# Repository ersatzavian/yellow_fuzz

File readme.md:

# Graduator

## What?

A bass fuzz for my good friend! Don't tell him, it's a surprise. Starting with a Boss MT-2 (I know, ew, don't tell anybody) because that's allegedly how Arion Salazar got most of his fuzz tone's on Third Eye Blind's self-titled (check out 2:20-2:30 in Graduate, of 4:10 in Thanks a Lot if you like yours with phaser). Hell yeah we want that, don't pretend you don't like that record. 

Formerly "yellow fuzz" after BRC's "yellow bikes" that happen to be green. Didn't like the sound of it, now it's the Graduator.

### Rev 01

Rev01 (non form-factor) has been built, brought up, and play tested. 

## Rev01 User Guide

[Electric Druid](https://electricdruid.net/boss-mt-2-metal-zone-pedal-analysis/) has an awesome write-up on the key circuit blocks in the original MT-2 design that's worth a read. If you want a comprehensive survey of the guts of this pedal, read that, then the mods section below, and you're done. 

### Controls

Controls are described by order in the signal chain, rather than physical layout. 

| Control | Original MT-2 Control, or Experiment | Circuit Block | What's it Do? |
| ------- | ------------------------------------ | ------------- | ------------- |
| Gain | Experiment | Distortion Block - First Op-Amp Stage Gain, P1.  | The "pre-distortion" gain block does two things: <ul><li> Applies a band-pass-filtered boost (the center frequency of this boost has a mod described separately). </li><li> Demands enough gain from op amp U1A to cause some distortion when at high gain setttings. </li></ul> In the original MT-2, the gain of this stage is fixed. In the graduator, the feedback resistance here can be reduced, which reduces the gain. If the pre-boost filter is ignored (or the pre-boost filter select switch is used to skip the pre-boost filter), this control doesn't really do much at all; the end result of reducing the gain here is audibly identical to reducing the "Distortion" control. But with a filter selected, this control lets you choose how much that initial band-pass boosts, which can be kind of interesting. Definitely won't be included in the form factor design, but merits playing around with while you're playing the the pre-boost filter select. |
| Pre-Boost Filter Select | Experiment | Distortion Block - First Op-Amp Stage Gyrator Select, SW1.  | As you can read about [here](https://sound-au.com/articles/gyrator-filters.htm), "gyrators" are nifty little active circuit blocks that let you make a thing that acts like an inductor out of a capacitor and a transistor or op-amp. Why not just use an inductor is a good question and is covered in that guide in good detail. For our purposes here, this control lets you pick between two filters, or a third disable setting: <ul><li> A stock filter which is described in the electric druid guide; it's a 36dB boost centered at 1 kHz with a "Q" of 2.8 ("Q", or "Quality Factor" describes how narrow and pointy that bandpass's frequency response is; a filter with high "Q" will be super pointy and really impact just its center frequency, while a filter with lower "Q" will be more gradual and wide and impact frequencies up and down the band around its center.).</li><li> A modified filter: 36 dB boost centered at 224 kHz, with a Q of 3.2. I made this mod to push the boost down into a range I thought might be better for a bass fuzz. </li><li> The disable setting just floats the switch terminal, which is kinda a bug because it takes the feedback (the "gain" control) out of the mix. You'll notice some volume variation going to and from this setting depending on where the "gain" is set. I may fix it. I may not. </li></ul>A bonus feature of this section is that one or both of these filter blocks could be retuned by changing a few parts, letting you do A/B comparison between a setting you like and a new setting you're considering. |
| Distortion | Original | Distortion Block - Second Op-Amp Stage Gain, P2A/B.  | Controls the gain of the second op-amp stage before the diode limiter that really clips the signal. Running this op-amp at high gain will boost the signal to the "rails", and you'll get very hard, square peaks, before you even hit the diode limiter. There are many different sources of distortion in this pedal, it's definitely not all up to just one circuit block to hammer your signal into a mess. |
| Diode Select Switches | Experiment | Distortion Block - Diode Limiting Stage, SW2 / SW3  | The core of this pedal, as with many distortion pedals, is the diode limiter. This stage takes your nice sine-shaped waveform and clips the peaks off of it when they exceed the forward voltage of the diodes. Different diodes have different forward voltages, and different response "shapes" as they effectively turn on and off. The internet is full of forums where people will swear that this diode does this or that and sounds this way or that way, and many of them are subjectively right but nearly all of them are oversimplifying the test case they're talking about. Since there are so many sources of distortion in this (and every) circuit, you're hearing them all. The diode is just part of it. Anyway, this mod lets you pick between three different kinds of diode for your limiter. Even weirder, it lets you choose the diode for the top and bottom half of your waveform separately, so you can produce very "asymmetric" distortion. Right now, you have: <ul><li> A Silicon diode, the generic [1N4148](https://www.diodes.com/assets/Datasheets/ds12019.pdf), with a forward voltage around 1V. </li><li> A Germanium diode, the generic [1N34A](https://www.nteinc.com/specs/original/1N34A.pdf), with a forward voltage around 1V. </li><li> An LED, [Kingbright WP7113QBC/D](https://www.mouser.com/datasheet/2/216/WP7113QBC-D-58299.pdf). This is a blue LED, and has a forward voltage of not less than 2.4V. This is really a bug; I should have used a red or yellow LED with a forward voltage closer to the other two, so that you could compare tone without comparing volume - you'll notice right away that the blue LED is louder than the other diodes. I like how it sounds, though, so I'm considering that a future experiment and letting it ride. </li></ul> Just like the pre-distortion boost section, this section is a great place to swap out components you're curious about and A/B test stuff. |
| Diode Series Resistance Control | Experiment | Distortion Block - Diode Limiting Stage, P3 / P4.  | Diode clipping can be very harsh and introduce harmonics that you wouldn't get from, say, output stage distortion in a tube amplifier, which can sound really buzzy and cheap and not great. In an attempt to prevent this, I added 1k potentiometers - variable resistors - in series with the diodes, to soften the "knee" when they turn on and off and try and reduce that fuzz. In practice, the EQ section of this pedal has way, way more impact on the harmonic content that makes it out of the pedal, and I find this control completely inaudible. |
| Post-Boost Filter Enables | Experiment | Distortion Block - after Diode Limiting Stage, SW4 / SW5.  | The original MT-2 includes this stage with both Gyrator sections included, which provides a "double-humped" bandpass boost. In the original, the two sections are: <ul><li> A ~5dB boost at 105 Hz with Q=14.6. </li><li> A ~10dB boost at 4.9 kHz with Q=2.2. </li></ul>In the graduator, the two sections are: <ul><li> A ~5dB boost at 333 Hz with Q=4.6. </li><li> The original ~10dB boost at 4.9 kHz with Q=2.2. </li></ul>There are really two mods here: <ul><li> I've moved the lower peak up the frequency spectrum and fattened it up a bit. </li><li> Both peaks can be enabled or disabled with the respective switches. </li></ul> This is a little more subtle to play with than I expected, and I like that. Try it out. |
| EQ - Low | Original | Tone Block | The original "low shelf" control, a band-pass filter centered at 105 Hz with a Q of 3.1, which can provide up to 20dB of cut or boost. The whole EQ section is covered very nicely with plots in the Electric Druid guide, highly recommend. |
| EQ - Mid Frequency | Original | Tone Block | The original "mid frequency" control, which controls the center of the mid band-pass filter. Filter center frequency can be swept from about 200 Hz to about 7 kHz. This control would be a lot better as a log taper pot, to spread the frequencies of interest logarithmically along the range of the pot, but a dual-ganged log-taper 50kΩ pot is not an easy thing to find. As a result, you'll hear this control really come to life between about 1 o-clock and 5 o-clock. |
| EQ - Mid | Original | Tone Block | Cut or boost up to 15 dB with the mid-band filter centered wherever you put it with the Mid Frequency knob. |
| EQ - High | Original | Tone Block | High Shelf EQ, begins to kick in around 1kHz, where it offers around 6 dB of cut or boost, and flattens around 10 kHz, where it offers around 20 kHz of cut or boost. | 
| Level | Original | Tone Block | You know what this does. | 
| Enable / Bypass | Original | Switching Section | You know what this does too. |

## Mods

| Change | Goal | Done |
| ------ | ---- | ---- |
| Make gyrators after clipping stage optional (see C24/C25, C20/C17) | Experiment with pedal character to reduce fizz and deliver more even tone to the eq section so I can hear the difference. | Yes |
| Add bypass option for preboost stage. | Try to reduce fizz. | Yes |
| Add series variable resistors (trim pots) to clipping diodes D3/D4. | Try to reduce fizz. | Yes |
| Add selector switch for 3 different diode options in each direction. | Experiment with higher Vf (LEDs) and give germanium a whirl. | Yes |

## Issues

### Rev01 (Non-Form-Factor)

| Issue | Workaround | Fix | Fixed in Master |
| ----- | ---------- | --- | --------------- |
| C2 and R6 ref designators are swapped. HTML BOM shows correct outlines. | Install per HTML BOM. | Swap ref des back. | |
| R4, R6-7, R12, R14-15, R17-18, R24-26, R33, R51 MPN is for 1k part, should be 10k (part description on BOM is correct, but MPN is wrong). | Install 10k part. | Update component in lib. | | 
| R14 and R15 ref des are colliding. | N/A | Fix in layout. | |
| NSVJ3910SB3T1G was replaced in order with J113, which is a through-hole part and won't fit. | Order correct part. | Make sure MPN in design is correct and orderable. | |
| PTV111-4420-A104 was missing from kit, got extra PTV112-4420-A104 instead. | Cut leads 1 and 2, bend 3-6 down to fit into pads 1-4 to use just one pot of the two in the package. | Order the right thing. | |
| PTV111-4420-A503 was missing from kit, got extra PTV112-4420-A503 instead. | Cut leads 1 and 2, bend 3-6 down to fit into pads 1-4 to use just one pot of the two in the package. | Order the right thing. | |
| Nichicon UST1H010MDD1TE footprint is wrong (C1, C19, C26, C36, C43, C46): lead spacing is nto correct, part leads are flared for wider spacing than footprint. | Bend leads back. | Correct footprint. | | 
| D6 missing MPN info. | N/A | Correct part library ref. | |
| No test points, doh. | N/A | Add some ground test points and stage-to-stage test points and jumpers. | |
| 22 Ohm series-R on power rail, why even would you do that? | Short that. | Remove that. | |
| Polarity marks on op-amps are not visible enough, and are obscured when sockets are installed (U1 was installed rotated 180 degrees in first build). | Note polarity carefully during build. | Improve op amp polarity marks. | |
| Pre-distortion boost gain pot P1 is backwards (CCW for more) | Turn it the other way, or snip top-side trace between pins 1-2, short pins 1-3.   | Correct in schematic. | |
| Dual pots installed in P5, P6, P7, and P9 with pins 3-6 slid over into pads 1-4 don't match design correctly. | Double-check pinout of these parts and revise rework used to place dual pots in single-pot footprints. | Use the parts on the BOM, duh. | |
| Duplicate TONE_OUT net names caused short across level pot.  | Cut extra trace on top layer.  | Remove duplicate net label. | |
| Incorrectly routed jack as center-positive, which makes the battery not work at all. | Cut and swap traces to make center-negative.  | Permanentify rework. | |
| Mid frequency control only does much between about 1-o-clock and 5-o-clock. | Use as is. | Try once more to find a log pot... good luck. | |
| Pre-boost filter select switch SW1 should probably have a resistor on its unused pole, rather than having fixed gain and taking the "gain" control out of the mix. |  |  |  |

## Parts Needed

### For Rev02 (Form-Factor)
* 1/4" Stereo Jack, Panel Mount with header footprint.
* 1/4" Mono Jack, Panel Mount with header footprint
* Re-evaluate all potentiometer tapers and footprints.

## Play testing notes

* It sounds... like an MT-2 with some stuff changed. 
* The pre-filter change is the most interesting, as swapping diode types. 
* Post-filters are also interesting, but a bit less so. 
* Still many settings that produce lots of unpleasant fizz. Tonally I'd still say it's "mostly bad with the ability to do some good things."
* Series-R on the dioes does exactly nothing. On the scope, it does visibly soften the knees a little, but by the time this has been through the tone section, that does the same thing. 
* Secondary control on the initial boost gain does exactly the same thing as the drive control. Might try playing with it a bit more with the pre-filter set to off, but for the most part just set it to 10 and leave it. 

## References

### Other Pedals I'm eyeing
* DOD FX91 Bass Overdrive
* Darkglass - Duality
* Zvex - Wooly Mammoth
* Death by Audio - Fuzz War
* Bass Big Muff
* MXR Bass Fuzz
* Fairfield Barbershop

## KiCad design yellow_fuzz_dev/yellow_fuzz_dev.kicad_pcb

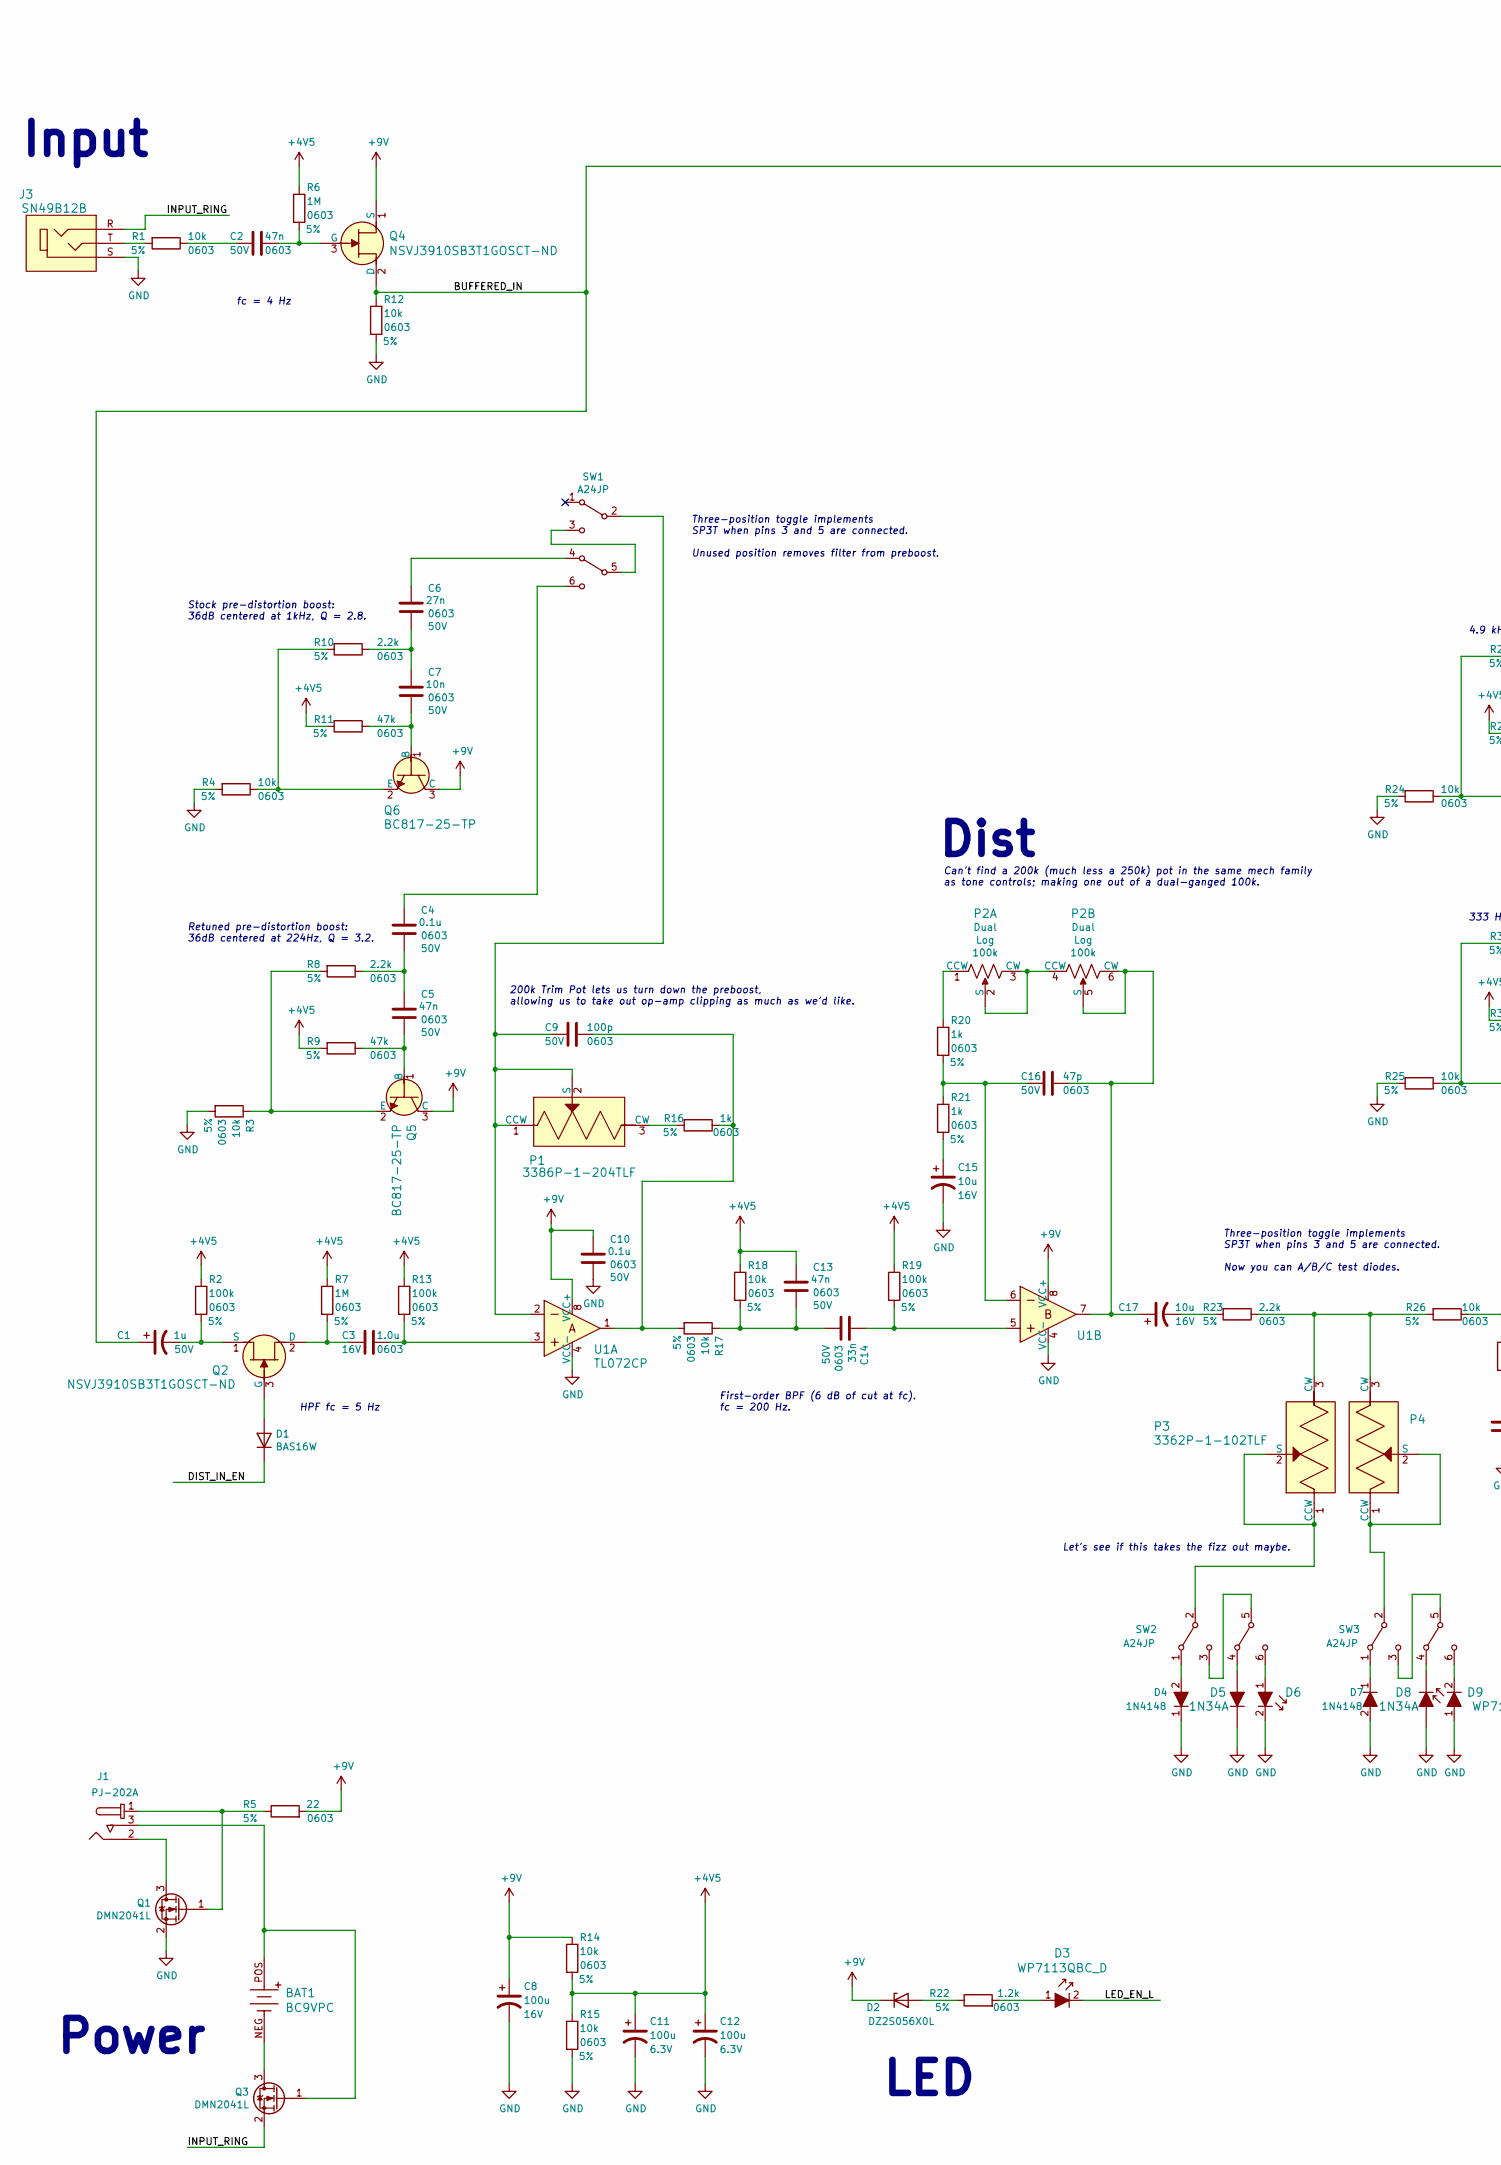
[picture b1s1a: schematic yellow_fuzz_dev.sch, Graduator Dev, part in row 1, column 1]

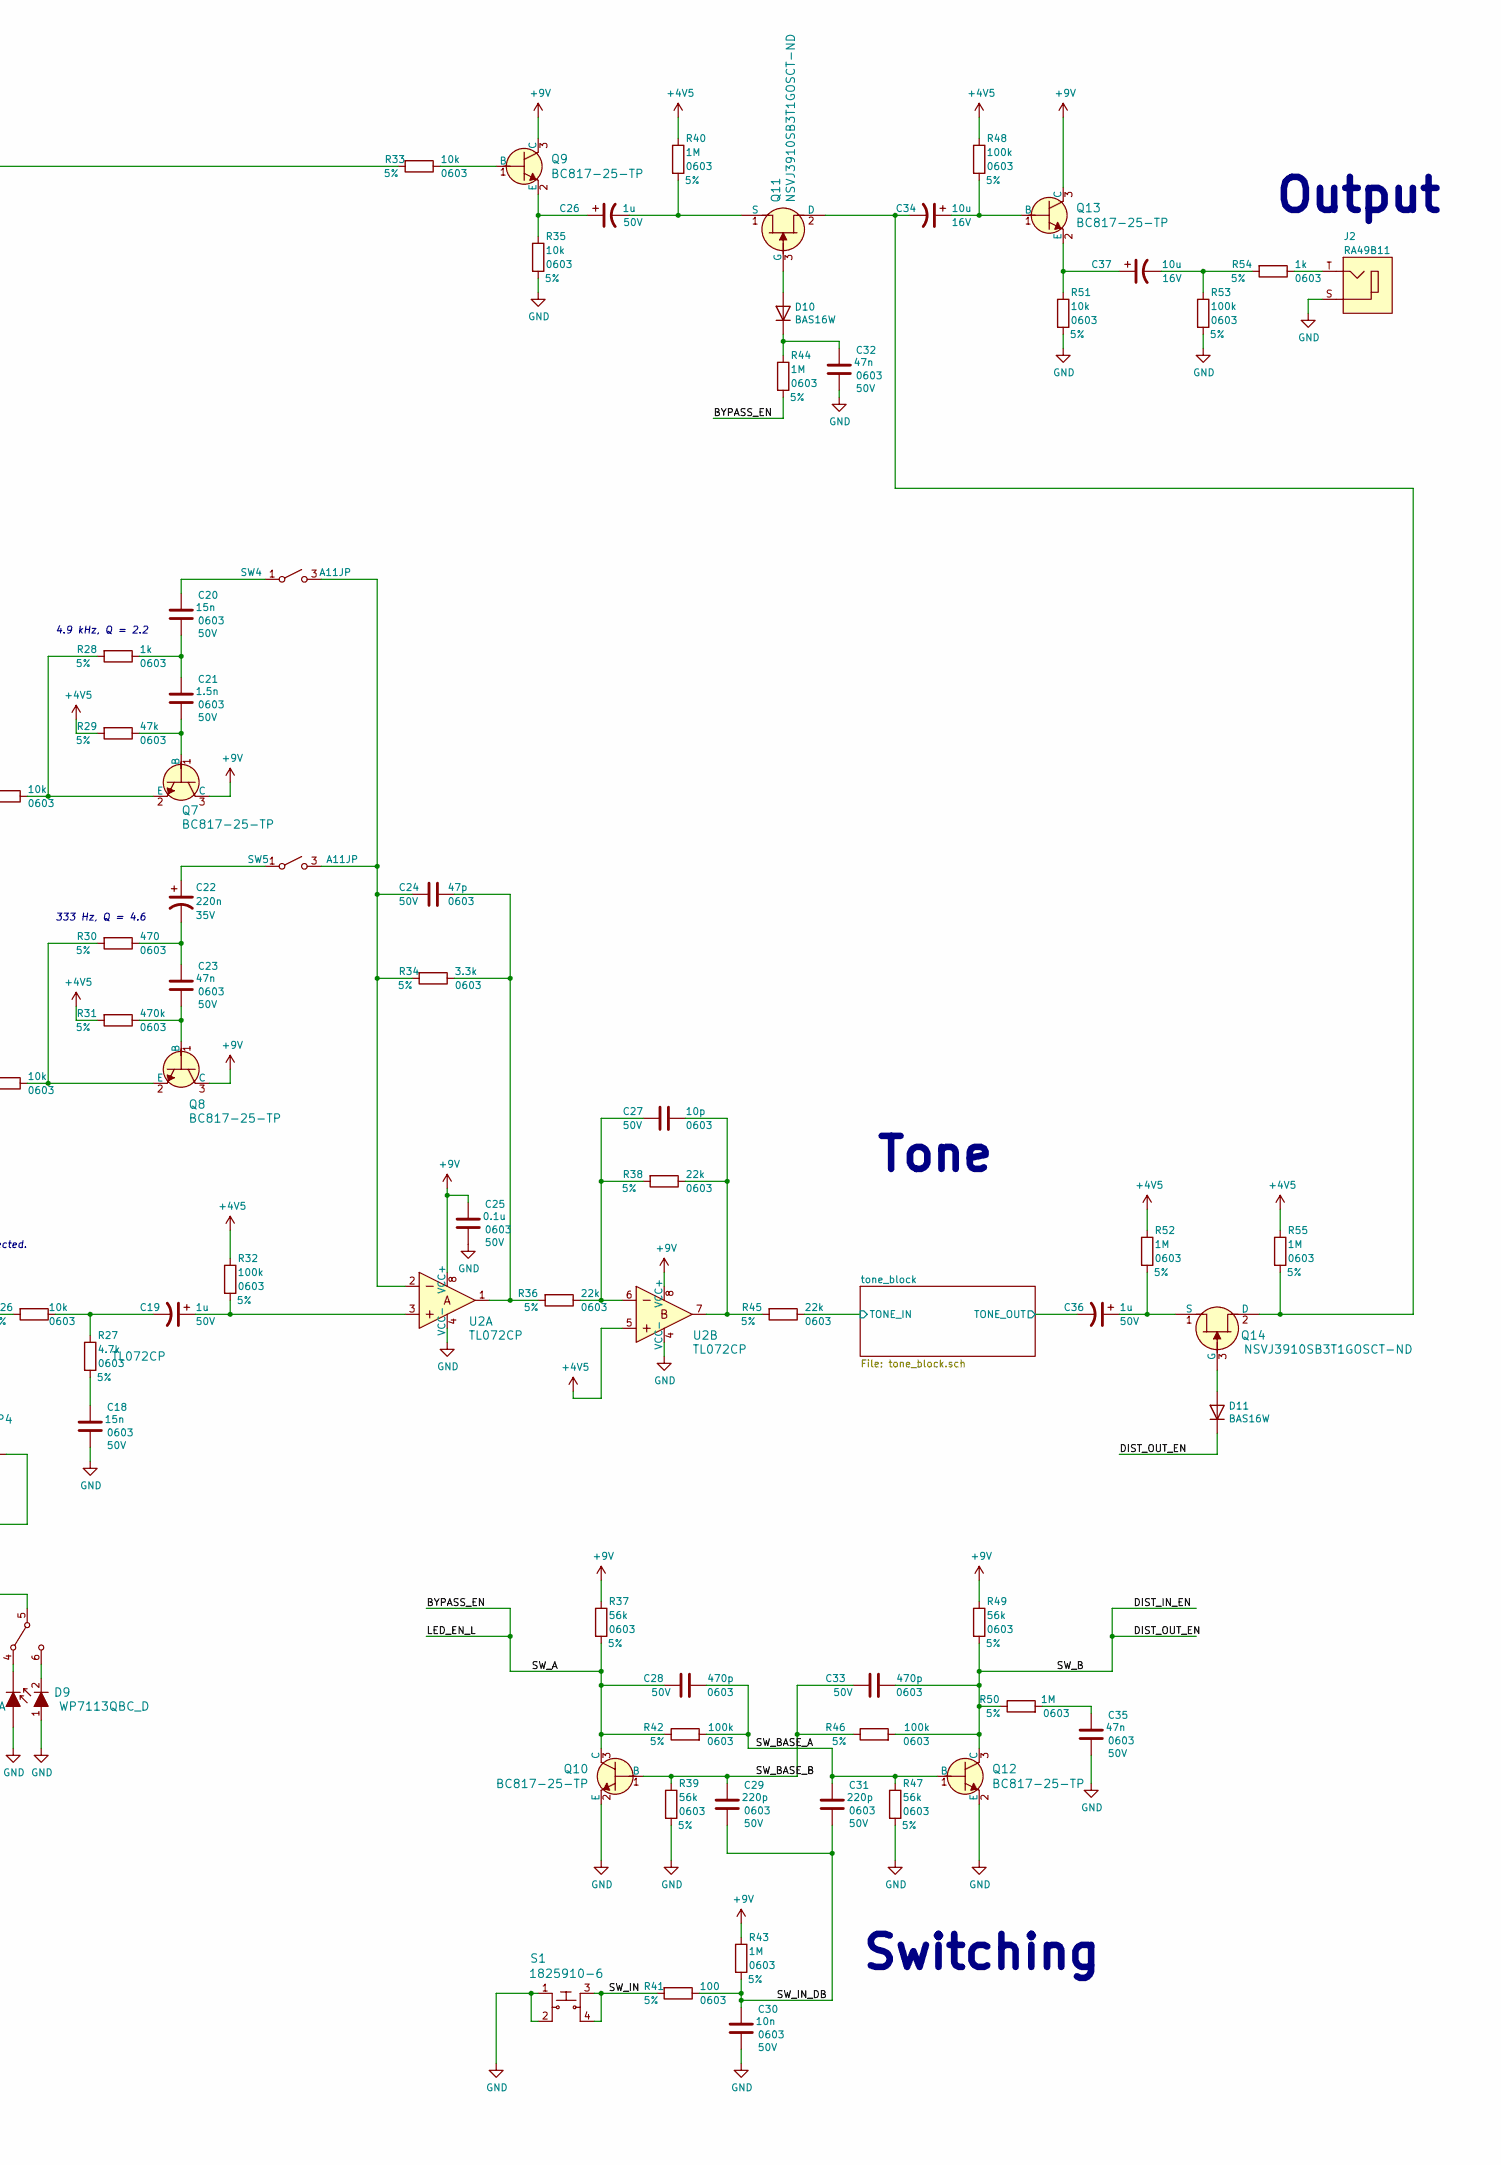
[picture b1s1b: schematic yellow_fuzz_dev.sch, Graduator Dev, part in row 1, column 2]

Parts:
BAT1: BC9VPC; Battery_Holder_9V_BC9VPC-ND; Manufacturer PN BC9VPC
C1, C19, C26, C36: 1u; CP_Radial_D4.0mm_P1.50mm; Voltage 50V; Manufacturer PN UST1H010MDD1TE
C2, C5, C13, C23, C32, C35: 47n; C_0603_1608Metric_Pad1.05x0.95mm_HandSolder; Voltage 50V; Manufacturer PN CC0603KRX7R9BB473
C3: 1.0u; C_0603_1608Metric_Pad1.05x0.95mm_HandSolder; Voltage 16V; Manufacturer PN CC0603ZRY5V7BB105
C4, C10, C25: 0.1u; C_0603_1608Metric_Pad1.05x0.95mm_HandSolder; Voltage 50V; Manufacturer PN C0603C104M5RACTU
C6: 27n; C_0603_1608Metric_Pad1.05x0.95mm_HandSolder; Voltage 50V; Manufacturer PN CC0603KRX7R9BB273
C7, C30: 10n; C_0603_1608Metric_Pad1.05x0.95mm_HandSolder; Voltage 50V; Manufacturer PN CC0603KPX7R9BB103
C8: 100u; CP_Radial_D5.0mm_P2.00mm; Voltage 16V; Manufacturer PN 860010372006
C9: 100p; C_0603_1608Metric_Pad1.05x0.95mm_HandSolder; Voltage 50V; Manufacturer PN CC0603JRNPO9BN101
C11, C12: 100u; CP_Radial_D5.0mm_P2.00mm; Voltage 6.3V; Manufacturer PN ESK107M6R3AC3AA
C14: 33n; C_0603_1608Metric_Pad1.05x0.95mm_HandSolder; Voltage 50V; Manufacturer PN CC0603KRX7R9BB333
C15, C17, C34, C37: 10u; CP_Radial_D5.0mm_P2.00mm; Voltage 16V; Manufacturer PN 860010372001
C16, C24: 47p; C_0603_1608Metric_Pad1.05x0.95mm_HandSolder; Voltage 50V; Manufacturer PN CC0603JRNPO9BN470
C18, C20: 15n; C_0603_1608Metric_Pad1.05x0.95mm_HandSolder; Voltage 50V; Manufacturer PN CC0603KRX7R9BB153
C21: 1.5n; C_0603_1608Metric_Pad1.05x0.95mm_HandSolder; Voltage 50V; Manufacturer PN CC0603KRX7R9BB152
C22: 220n; CP_Radial_D5.0mm_P2.00mm; Voltage 35V; Manufacturer PN UVR2AR22MDD
C27: 10p; C_0603_1608Metric_Pad1.05x0.95mm_HandSolder; Voltage 50V; Manufacturer PN CC0603JRNPO9BN100
C28, C33: 470p; C_0603_1608Metric_Pad1.05x0.95mm_HandSolder; Voltage 50V; Manufacturer PN CC0603KRX7R9BB471
C29, C31: 220p; C_0603_1608Metric_Pad1.05x0.95mm_HandSolder; Voltage 50V; Manufacturer PN CC0603KRX7R9BB221
D1, D10, D11: BAS16W; SOT-323_SC-70; Manufacturer PN BAS16WT1G
D2: DZ2S056X0L; D_SOD-523; Manufacturer PN DZ2S056M0L
D3, D6, D9: WP7113QBC_D; LED_5mm_Radial; Manufacturer PN WP7113QBC/D
D4, D7: 1N4148; Diode_DO-35_P10mm; Manufacturer PN 1N4148
D5, D8: 1N34A; DO-35; Manufacturer PN 1N34A
J1: PJ-202A; Barrel_Jack_5.5mmODx2.1mmID_PJ-202A; Manufacturer PN PJ-202A
J2: RA49B11; Headphone_Jack_6.35mm_SN49B12B; Manufacturer PN RA49B11
J3: SN49B12B; Headphone_Jack_6.35mm_SN49B12B; Manufacturer PN SN49B12B
P1: 3386P-1-204TLF; 3386P; Manufacturer PN 3386P-1-204TLF
P2: PTV112-4420A-A104; Potentiometer_Bourns_PTV112_3417A_Dual_Vertical; Manufacturer Part Number PTV112-4420A-A104
P3, P4: 3362P-1-102TLF; 3362PT; Manufacturer PN 3362P-1-102TLF
Q1, Q3: DMN2041L; SOT-23; Manufacturer PN DMN2041L-7
Q2, Q4, Q11, Q14: NSVJ3910SB3T1GOSCT-ND; SOT-23_Handsoldering; Manufacturer PN NSVJ3910SB3T1G
Q5, Q6, Q7, Q8, Q9, Q10, Q12, Q13: BC817-25-TP; SOT-23-3; Manufacturer PN BC817-25-TP
R1, R3, R4, R12, R14, R15, R17, R18, R24, R25, R26, R33, R35, R51: 10k; R_0603_1608Metric_Pad1.05x0.95mm_HandSolder; Tolerance 5%; Manufacturer PN RC0603JR-071KL
R2, R13, R19, R32, R42, R46, R48, R53: 100k; R_0603_1608Metric_Pad1.05x0.95mm_HandSolder; Tolerance 5%; Manufacturer PN CR0603-JW-104ELF
R5: 22; R_0603_1608Metric_Pad1.05x0.95mm_HandSolder; Tolerance 5%; Manufacturer PN RC0603FR-0722RL
R6, R7, R40, R43, R44, R50, R52, R55: 1M; R_0603_1608Metric_Pad1.05x0.95mm_HandSolder; Tolerance 5%; Manufacturer PN RC0201JR-071ML
R8, R10, R23: 2.2k; R_0603_1608Metric_Pad1.05x0.95mm_HandSolder; Tolerance 5%; Manufacturer PN ERJ-3GEYJ222V
R9, R11, R29: 47k; R_0603_1608Metric_Pad1.05x0.95mm_HandSolder; Tolerance 5%; Manufacturer PN RC0603JR-0747KL
R16, R20, R21, R28, R54: 1k; R_0603_1608Metric_Pad1.05x0.95mm_HandSolder; Tolerance 5%; Manufacturer PN RC0603JR-071KL
R22: 1.2k; R_0603_1608Metric_Pad1.05x0.95mm_HandSolder; Tolerance 5%; Manufacturer PN ESR03EZPJ122
R27: 4.7k; R_0603_1608Metric_Pad1.05x0.95mm_HandSolder; Tolerance 5%; Manufacturer PN RC0603JR-074K7L
R30: 470; R_0603_1608Metric_Pad1.05x0.95mm_HandSolder; Tolerance 5%; Manufacturer PN RC0603JR-07470RL
R31: 470k; R_0603_1608Metric_Pad1.05x0.95mm_HandSolder; Tolerance 5%; Manufacturer PN RC0603JR-07470KL
R34: 3.3k; R_0603_1608Metric_Pad1.05x0.95mm_HandSolder; Tolerance 5%; Manufacturer PN CRGCQ0603J3K3
R36, R38, R45: 22k; R_0603_1608Metric_Pad1.05x0.95mm_HandSolder; Tolerance 5%; Manufacturer PN RC0603JR-0722KL
R37, R39, R47, R49: 56k; R_0603_1608Metric_Pad1.05x0.95mm_HandSolder; Tolerance 5%; Manufacturer PN RC0603JR-0756KL
R41: 100; R_0603_1608Metric_Pad1.05x0.95mm_HandSolder; Tolerance 5%; Manufacturer PN ESR03EZPJ101
S1: 1825910-6; Switch_Tactile_THT_6x6mm; Manufacturer PN 1825910-6
SW1, SW2, SW3: SW_SP3T_A24JP; A24JP; Manufacturer PN A24JP
SW4, SW5: SW_SPST_A11JP; A11JP; Manufactuer PN A11JP
U1, U2: TL072CP; DIP-8_W7.62mm; Manufacturer PN TL072CP

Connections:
+4V: C11.1, C12.1, C13.1, R2.1, R6.1, R7.1, R9.2, R11.2, R13.1, R14.2, R15.1, R18.1, R19.1, R29.2, R31.2, R32.1, R40.1, R48.1, R52.1, R55.1, U2.5; also elsewhere on the board
+9V: C8.1, C10.1, C25.1, D2.1 (K), Q4.1 (S), Q5.3 (C), Q6.3 (C), Q7.3 (C), Q8.3 (C), Q9.3 (C), Q13.3 (C), R5.2, R14.1, R37.1, R43.1, R49.1, U1.8 (VCC+), U2.8 (VCC+); also elsewhere on the board
/BUFFERED_IN: C1.1, Q4.2 (D), R12.1, R33.2
/BYPASS_EN: C28.1, D3.2, Q10.3 (C), R37.2, R42.1, R44.2
/DIST_IN_EN: C33.2, D1.3 (K), D11.3 (K), Q12.3 (C), R46.2, R49.2, R50.1
/INPUT_RING: J3.R, Q3.2 (S)
/SW_BASE_A: C28.2, C31.1, Q12.1 (B), R42.2, R47.1
/SW_BASE_B: C29.1, C33.1, Q10.1 (B), R39.1, R46.1
/SW_IN: R41.2, S1.3, S1.4
/SW_IN_DB: C29.2, C30.1, C31.2, R41.1, R43.2
/tone_block/TONE_IN: R45.1; also elsewhere on the board
/tone_block/TONE_OUT: C36.2; also elsewhere on the board
GND: C8.2, C10.2, C11.2, C12.2, C15.2, C18.2, C25.2, C30.2, C32.2, C35.2, D4.1, D5.K, D6.2, D7.2, D8.A, D9.1, J2.S, J3.S, Q1.2 (S), Q10.2 (E), Q12.2 (E), R3.2, R4.2, R12.2, R15.2, R24.2, R25.2, R35.2, R39.2, R47.2, R51.2, R53.2, S1.1, S1.2, U1.4 (VCC-), U2.4 (VCC-); also elsewhere on the board
unnamed: BAT1.NEG, Q3.3 (D)
unnamed: BAT1.POS, J1.3, Q3.1 (G)
unnamed: C1.2, Q2.1 (S), R2.2
unnamed: C2.1, Q4.3 (G), R6.2
unnamed: C2.2, R1.1
unnamed: C3.1, R13.2, U1.3
unnamed: C3.2, Q2.2 (D), R7.2
unnamed: C4.1, SW1.6
unnamed: C4.2, C5.1, R8.1
unnamed: C5.2, Q5.1 (B), R9.1
unnamed: C6.1, SW1.4
unnamed: C6.2, C7.1, R10.1
unnamed: C7.2, Q6.1 (B), R11.1
unnamed: C9.1, R16.1, R17.2, U1.1
unnamed: C9.2, P1.1 (CCW), P1.2 (S), SW1.2, U1.2
unnamed: C13.2, C14.2, R17.1, R18.2
unnamed: C14.1, R19.2, U1.5
unnamed: C15.1, R21.2
unnamed: C16.1, C17.1, P2.5 (S), P2.6 (CW), U1.7
unnamed: C16.2, R20.2, R21.1, U1.6
unnamed: C17.2, R23.2
unnamed: C18.1, R27.2
unnamed: C19.1, R32.2, U2.3
unnamed: C19.2, R26.1, R27.1
unnamed: C20.1, SW4.1 (A)
unnamed: C20.2, C21.1, R28.1
unnamed: C21.2, Q7.1 (B), R29.1
unnamed: C22.1, SW5.1 (A)
unnamed: C22.2, C23.1, R30.1
unnamed: C23.2, Q8.1 (B), R31.1
unnamed: C24.1, R34.1, R36.2, U2.1
unnamed: C24.2, R34.2, SW4.3 (B), SW5.3 (B), U2.2
unnamed: C26.1, Q9.2 (E), R35.1
unnamed: C26.2, Q11.1 (S), R40.2
unnamed: C27.1, R38.1, R45.2, U2.7
unnamed: C27.2, R36.1, R38.2, U2.6
unnamed: C32.1, D10.3 (K), R44.1
unnamed: C34.1, Q13.1 (B), R48.2
unnamed: C34.2, Q11.2 (D), Q14.2 (D), R55.2
unnamed: C35.1, R50.2
unnamed: C36.1, Q14.1 (S), R52.2
unnamed: C37.1, Q13.2 (E), R51.1
unnamed: C37.2, R53.1, R54.2
unnamed: D1.1 (A), Q2.3 (G)
unnamed: D2.2 (A), R22.1
unnamed: D3.1, R22.2
unnamed: D4.2, SW2.1
unnamed: D5.A, SW2.4
unnamed: D6.1, SW2.6
unnamed: D7.1, SW3.1
unnamed: D8.K, SW3.4
unnamed: D9.2, SW3.6
unnamed: D10.1 (A), Q11.3 (G)
unnamed: D11.1 (A), Q14.3 (G)
unnamed: J1.1, Q1.1 (G), R5.1
unnamed: J1.2, Q1.3 (D)
unnamed: J2.T, R54.1
unnamed: J3.T, R1.2
unnamed: P1.3 (CW), R16.2
unnamed: P2.1 (CCW), R20.1
unnamed: P2.2 (S), P2.3 (CW), P2.4 (CCW)
unnamed: P3.1 (CCW), P3.2 (S), SW2.2
unnamed: P3.3 (CW), P4.3 (CW), R23.1, R26.2
unnamed: P4.1 (CCW), P4.2 (S), SW3.2
unnamed: Q5.2 (E), R3.1, R8.2
unnamed: Q6.2 (E), R4.1, R10.2
unnamed: Q7.2 (E), R24.1, R28.2
unnamed: Q8.2 (E), R25.1, R30.2
unnamed: Q9.1 (B), R33.1
unnamed: SW1.3, SW1.5
unnamed: SW2.3, SW2.5
unnamed: SW3.3, SW3.5

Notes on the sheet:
LED
Dist
Input
Power
Output
Switching
Stock pre-distortion boost: 36dB centered at 1kHz, Q = 2.8.
fc = 4 Hz
HPF fc = 5 Hz
Retuned pre-distortion boost: 36dB centered at 224Hz, Q = 3.2.
First-order BPF (6 dB of cut at fc). fc = 200 Hz.
Tone
333 Hz, Q = 4.6
4.9 kHz, Q = 2.2
Three-position toggle implements SP3T when pins 3 and 5 are connected. Unused position removes filter from preboost.
Three-position toggle implements SP3T when pins 3 and 5 are connected. Now you can A/B/C test diodes.
Let’s see if this takes the fizz out maybe.
200k Trim Pot lets us turn down the preboost, allowing us to take out op-amp clipping as much as we’d like.
Can’t find a 200k (much less a 250k) pot in the same mech family as tone controls; making one out of a dual-ganged 100k.

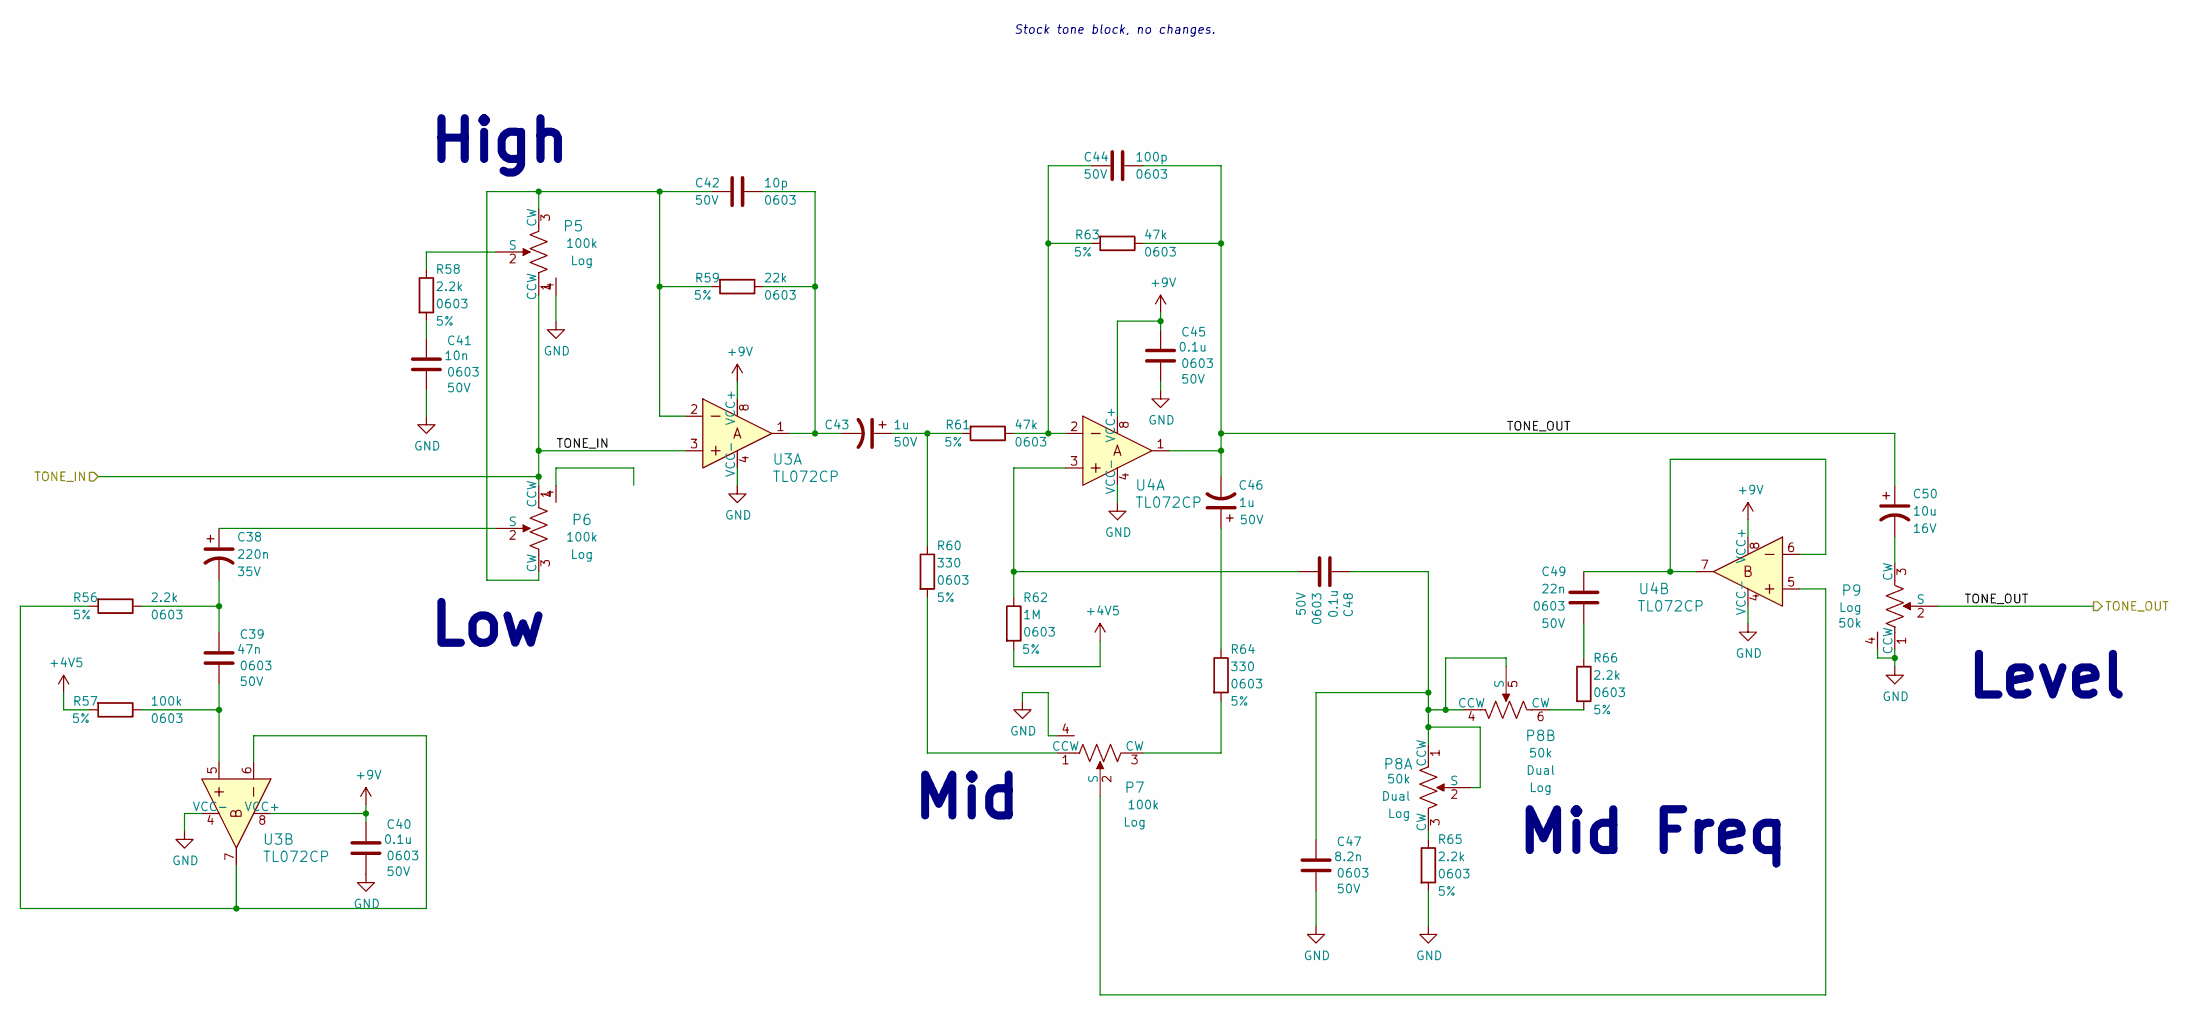
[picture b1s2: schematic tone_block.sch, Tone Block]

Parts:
C38: 220n; CP_Radial_D5.0mm_P2.00mm; Voltage 35V; Manufacturer PN UVR2AR22MDD
C39: 47n; C_0603_1608Metric_Pad1.05x0.95mm_HandSolder; Voltage 50V; Manufacturer PN CC0603KRX7R9BB473
C40, C45, C48: 0.1u; C_0603_1608Metric_Pad1.05x0.95mm_HandSolder; Voltage 50V; Manufacturer PN C0603C104M5RACTU
C41: 10n; C_0603_1608Metric_Pad1.05x0.95mm_HandSolder; Voltage 50V; Manufacturer PN CC0603KPX7R9BB103
C42: 10p; C_0603_1608Metric_Pad1.05x0.95mm_HandSolder; Voltage 50V; Manufacturer PN CC0603JRNPO9BN100
C43, C46: 1u; CP_Radial_D4.0mm_P1.50mm; Voltage 50V; Manufacturer PN UST1H010MDD1TE
C44: 100p; C_0603_1608Metric_Pad1.05x0.95mm_HandSolder; Voltage 50V; Manufacturer PN CC0603JRNPO9BN101
C47: 8.2n; C_0603_1608Metric_Pad1.05x0.95mm_HandSolder; Voltage 50V; Manufacturer PN CC0603KRX7R8BB822
C49: 22n; C_0603_1608Metric_Pad1.05x0.95mm_HandSolder; Voltage 50V; Manufacturer PN CC0603KRX7R9BB223
C50: 10u; CP_Radial_D5.0mm_P2.00mm; Voltage 16V; Manufacturer PN 860010372001
P5, P6, P7: PTV111-4420A-A104; Potentiometer_Bourns_PTV111_4420A_Single_Vertical; Manufacturer PN PTV111-4420A-A104
P8: PTV112-4420A-A503; Potentiometer_Bourns_PTV112_3417A_Dual_Vertical; Manufacturer PN PTV112-4420A-A503
P9: PTV111-4420A-A503; Potentiometer_Bourns_PTV111_4420A_Single_Vertical; Manufacturer PN PTV111-4420A-A503
R56, R58, R65, R66: 2.2k; R_0603_1608Metric_Pad1.05x0.95mm_HandSolder; Tolerance 5%; Manufacturer PN ERJ-3GEYJ222V
R57: 100k; R_0603_1608Metric_Pad1.05x0.95mm_HandSolder; Tolerance 5%; Manufacturer PN CR0603-JW-104ELF
R59: 22k; R_0603_1608Metric_Pad1.05x0.95mm_HandSolder; Tolerance 5%; Manufacturer PN RC0603JR-0722KL
R60, R64: 330; R_0603_1608Metric_Pad1.05x0.95mm_HandSolder; Tolerance 5%; Manufacturer PN CR0603-JW-331ELF
R61, R63: 47k; R_0603_1608Metric_Pad1.05x0.95mm_HandSolder; Tolerance 5%; Manufacturer PN RC0603JR-0747KL
R62: 1M; R_0603_1608Metric_Pad1.05x0.95mm_HandSolder; Tolerance 5%; Manufacturer PN RC0201JR-071ML
U3, U4: TL072CP; DIP-8_W7.62mm; Manufacturer PN TL072CP

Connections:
+4V: R57.2, R62.2; also elsewhere on the board
+9V: C40.1, C45.1, U3.8 (VCC+), U4.8 (VCC+); also elsewhere on the board
/tone_block/TONE_IN: P5.1 (CCW), P6.1 (CCW), U3.3; also elsewhere on the board
/tone_block/TONE_OUT: C44.1, C46.2, C50.1, P9.2 (S), R63.1, U4.1; also elsewhere on the board
GND: C40.2, C41.2, C45.2, C47.2, P5.4, P7.4, P9.1 (CCW), P9.4, R65.2, U3.4 (VCC-), U4.4 (VCC-); also elsewhere on the board
unnamed: C38.1, P6.2 (S)
unnamed: C38.2, C39.1, R56.1
unnamed: C39.2, R57.1, U3.5
unnamed: C41.1, R58.2
unnamed: C42.1, C43.2, R59.1, U3.1
unnamed: C42.2, P5.3 (CW), P6.3 (CW), R59.2, U3.2
unnamed: C43.1, R60.1, R61.2
unnamed: C44.2, R61.1, R63.2, U4.2
unnamed: C46.1, R64.1
unnamed: C47.1, C48.1, P8.1 (CCW), P8.2 (S), P8.4 (CCW), P8.5 (S)
unnamed: C48.2, R62.1, U4.3
unnamed: C49.1, U4.6, U4.7
unnamed: C49.2, R66.1
unnamed: C50.2, P9.3 (CW)
unnamed: P5.2 (S), R58.1
unnamed: P7.1 (CCW), R60.2
unnamed: P7.2 (S), U4.5
unnamed: P7.3 (CW), R64.2
unnamed: P8.3 (CW), R65.1
unnamed: P8.6 (CW), R66.2
unnamed: R56.2, U3.6, U3.7

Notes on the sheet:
Low
High
Mid
Mid Freq
Level
Stock tone block, no changes.
